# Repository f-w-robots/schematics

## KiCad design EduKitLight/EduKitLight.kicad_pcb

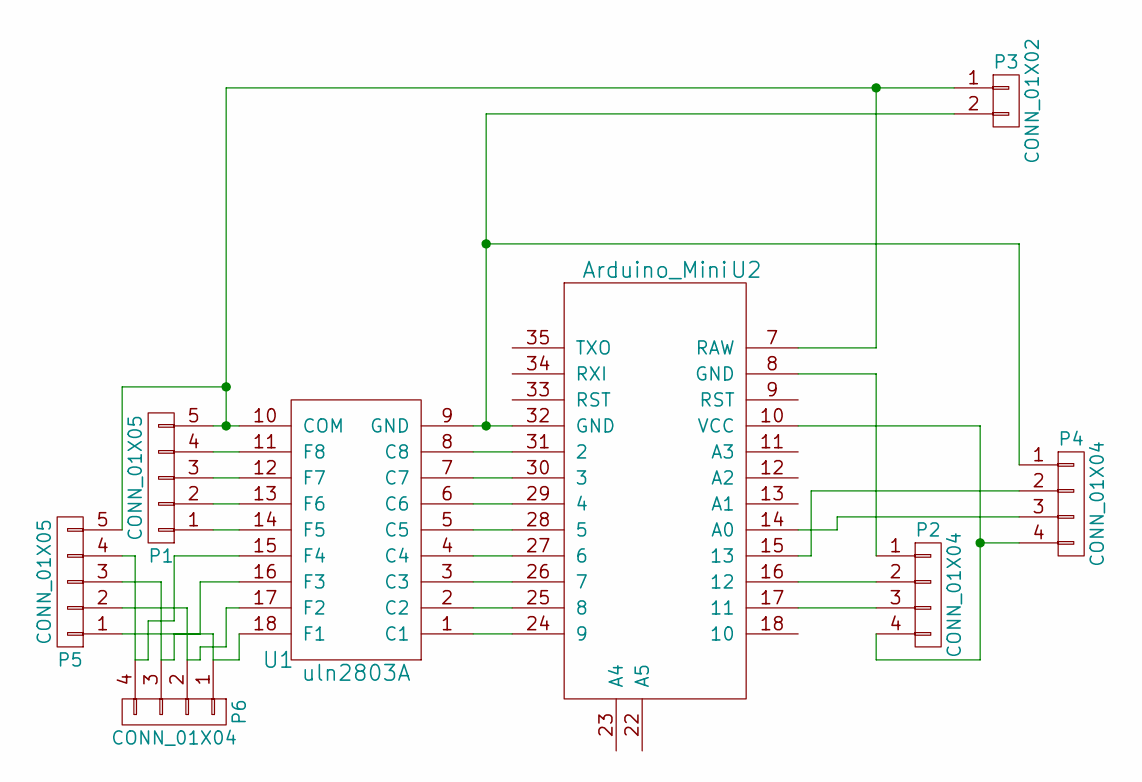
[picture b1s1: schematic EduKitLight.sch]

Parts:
P1, P5: CONN_01X05; Pin_Header_Straight_1x05
P2, P4, P6: CONN_01X04; Pin_Header_Straight_1x04
P3: CONN_01X02; Pin_Header_Straight_1x02
U1: uln2803A; DIP-18_W7.62mm
U2: Arduino_Mini; arduino_mini_pro

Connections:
unnamed: P1.1, U1.14 (F5)
unnamed: P1.2, U1.13 (F6)
unnamed: P1.3, U1.12 (F7)
unnamed: P1.4, U1.11 (F8)
unnamed: P1.5, P3.1, P5.5, U1.10 (COM), U2.7 (RAW)
unnamed: P2.1, U2.8 (GND)
unnamed: P2.2, U2.16 (12)
unnamed: P2.3, U2.17 (11)
unnamed: P2.4, P4.4, U2.10 (VCC)
unnamed: P3.2, P4.1, U1.9 (GND), U2.32 (GND)
unnamed: P4.2, U2.15 (13)
unnamed: P4.3, U2.14 (A0)
unnamed: P5.1, P6.1, U1.18 (F1)
unnamed: P5.2, P6.2, U1.17 (F2)
unnamed: P5.3, P6.3, U1.16 (F3)
unnamed: P5.4, P6.4, U1.15 (F4)
unnamed: U1.1 (C1), U2.24 (9)
unnamed: U1.2 (С2), U2.25 (8)
unnamed: U1.3 (С3), U2.26 (7)
unnamed: U1.4 (С4), U2.27 (6)
unnamed: U1.5 (С5), U2.28 (5)
unnamed: U1.6 (С6), U2.29 (4)
unnamed: U1.7 (С7), U2.30 (3)
unnamed: U1.8 (С8), U2.31 (2)

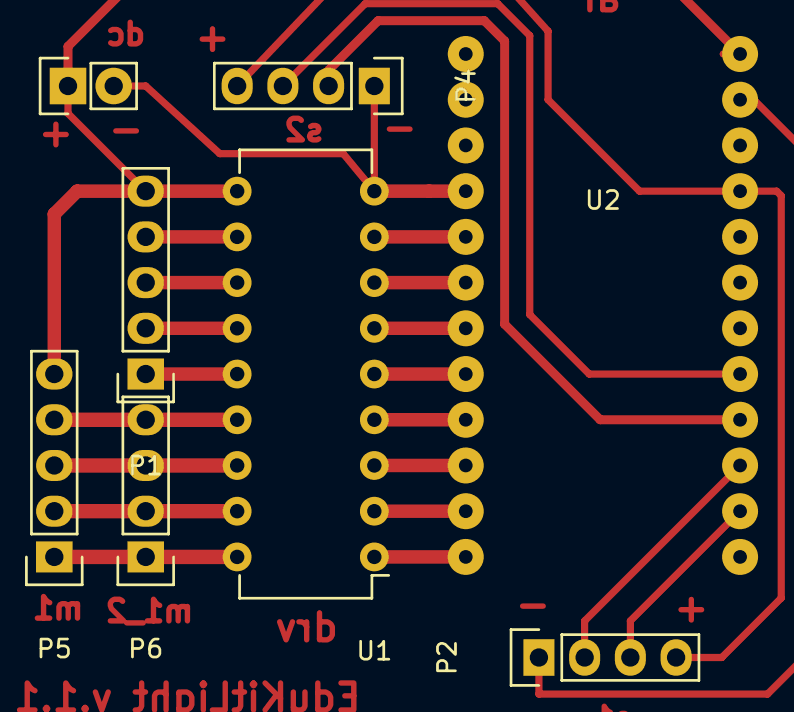
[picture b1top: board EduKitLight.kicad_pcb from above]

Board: 2 copper layers, 8 parts (0 on the bottom side), 24 nets.

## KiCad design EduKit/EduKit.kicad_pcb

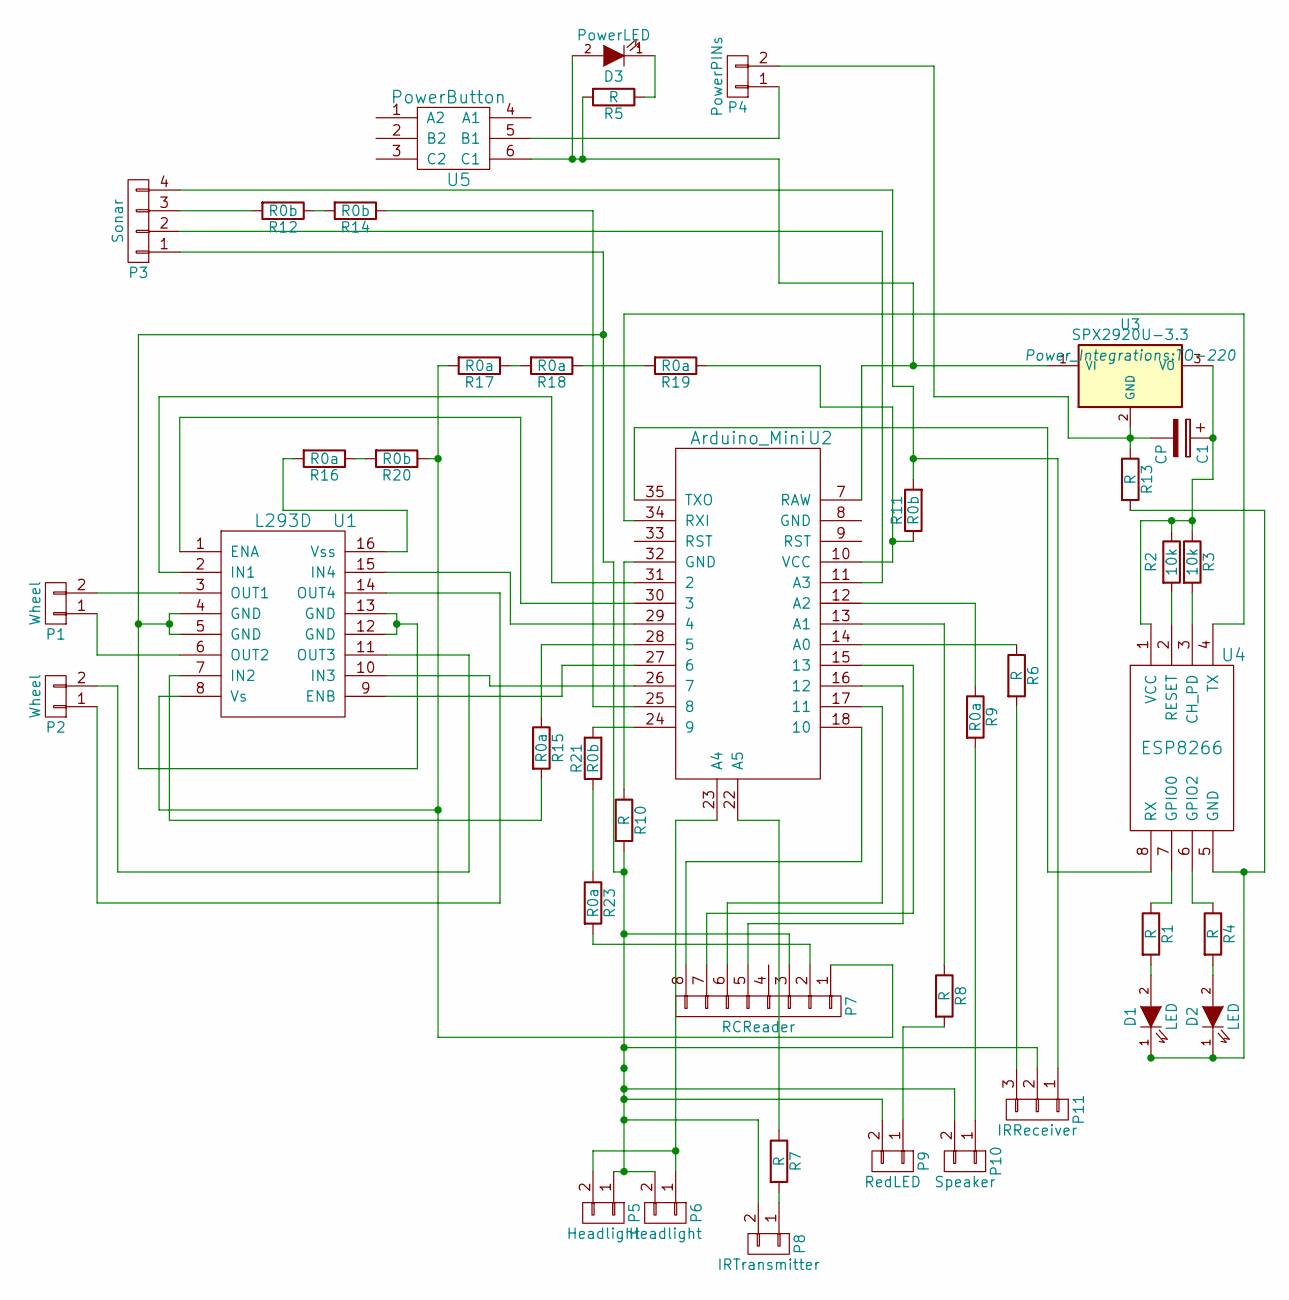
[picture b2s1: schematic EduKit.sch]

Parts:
C1: CP; CPR10X16
D1, D2: LED; LED-5MM
D3: PowerLED; LED-5MM
P1, P2: Wheel; Pin_Header_Straight_1x02
P3: Sonar; Pin_Header_Straight_1x04
P4: PowerPINs; Pin_Header_Straight_1x02
P5, P6: Headlight; Pin_Header_Straight_1x02
P7: RCReader; Pin_Header_Straight_1x08
P8: IRTransmitter; Pin_Header_Straight_1x02
P9: RedLED; Pin_Header_Straight_1x02
P10: Speaker; Pin_Header_Straight_1x02
P11: IRReceiver; Pin_Header_Straight_1x03
R1, R4, R5: R; Resistor_Horizontal_RM7mm
R2, R3: 10k; Resistor_Horizontal_RM7mm
R6, R7, R8, R10, R13: R; R_1206
R9, R15, R16, R18, R19, R23: R0a; R_1206
R11, R12, R14, R20, R21: R0b; R_2512
R17: R0a; R_2512
U1: L293D; DIP-16_W7.62mm
U2: Arduino_Mini; arduino_mini_pro
U3: SPX2920U-3.3; TO-220
U4: ESP8266
U5: PowerButton; button

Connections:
unnamed: C1.1, R2.1, R3.1, U3.3 (VO), U4.1 (VCC)
unnamed: C1.2, P4.2, R13.1, U3.2 (GND)
unnamed: D1.1 (K), D2.1 (K), R13.2, U4.5 (GND)
unnamed: D1.2 (A), R1.2
unnamed: D2.2 (A), R4.2
unnamed: D3.1 (K), R5.1
unnamed: D3.2 (A), R5.2, U2.7 (RAW), U3.1 (VI), U5.6 (C1)
unnamed: P1.1, U1.6 (OUT2)
unnamed: P1.2, U1.3 (OUT1)
unnamed: P2.1, U1.14 (OUT4)
unnamed: P2.2, U1.11 (OUT3)
unnamed: P3.2, U2.11 (A3)
unnamed: P3.3, R12.2
unnamed: P4.1, U5.5 (B1)
unnamed: P5.2, P6.1, U2.23 (A4)
unnamed: P7.1, R17.2, R20.1, U1.8 (Vs)
unnamed: P7.2, R23.2
unnamed: P7.5, U2.16 (12)
unnamed: P7.6, U2.17 (11)
unnamed: P7.7, U2.15 (13)
unnamed: P7.8, U2.18 (10)
unnamed: P8.1, R7.2
unnamed: P9.1, R8.2
unnamed: P10.1, R9.2
unnamed: P3.1, P5.1, P6.2, P7.3, P8.2, P9.2, P10.2, P11.2, R10.2, U1.4 (GND), U1.5 (GND), U1.12 (GND), U1.13 (GND)
unnamed: P3.4, P11.1, R11.2
unnamed: P11.3, R6.2
unnamed: R1.1, U4.7 (GPIO0)
unnamed: R2.2, U4.2 (RESET)
unnamed: R3.2, U4.3 (CH_PD)
unnamed: R4.1, U4.6 (GPIO2)
unnamed: R6.1, U2.14 (A0)
unnamed: R7.1, U2.22 (A5)
unnamed: R8.1, U2.13 (A1)
unnamed: R9.1, U2.12 (A2)
unnamed: R10.1, U2.32 (GND)
unnamed: R11.1, R19.1, U2.10 (VCC)
unnamed: R12.1, R14.2
unnamed: R14.1, U2.25 (8)
unnamed: R15.1, U2.28 (5)
unnamed: R15.2, U1.7 (IN2)
unnamed: R16.1, R20.2
unnamed: R16.2, U1.16 (Vss)
unnamed: R17.1, R18.2
unnamed: R18.1, R19.2
unnamed: R21.1, R23.1
unnamed: R21.2, U2.24 (9)
unnamed: U1.1 (ENA), U2.30 (3)
unnamed: U1.2 (IN1), U2.31 (2)
unnamed: U1.9 (ENB), U2.27 (6)
unnamed: U1.10 (IN3), U2.26 (7)
unnamed: U1.15 (IN4), U2.29 (4)
unnamed: U2.34 (RXI), U4.4 (TX)
unnamed: U2.35 (TXO), U4.8 (RX)

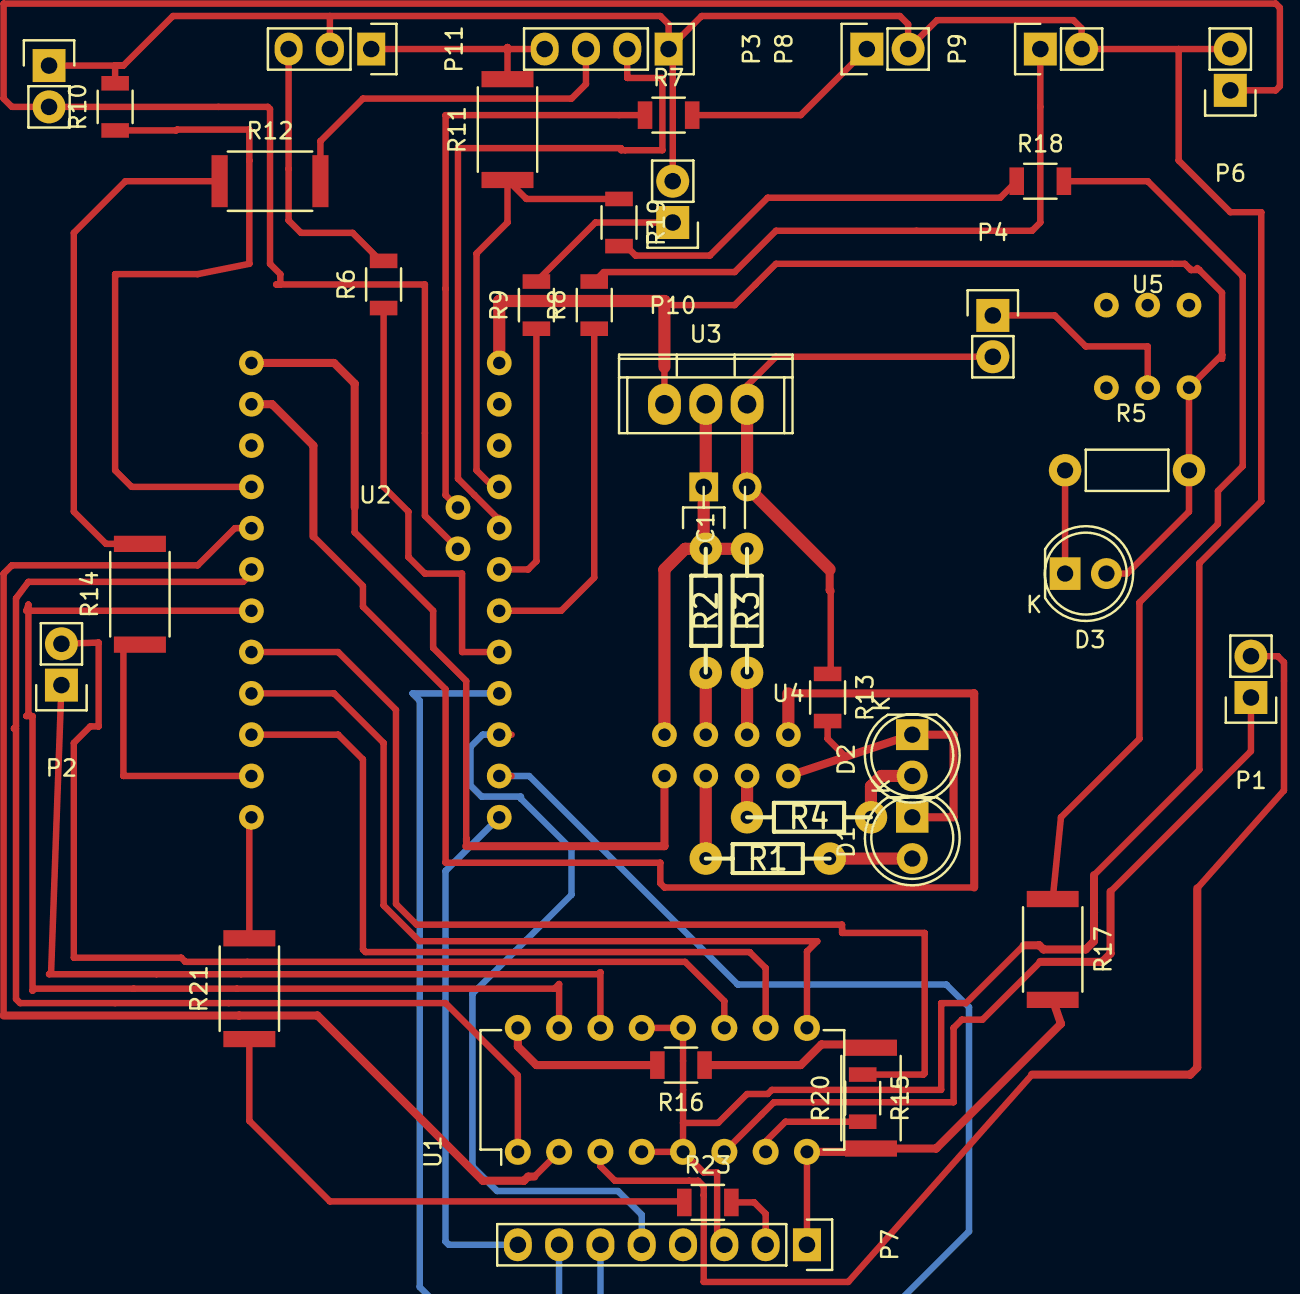
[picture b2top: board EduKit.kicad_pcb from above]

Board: 2 copper layers, 42 parts (0 on the bottom side), 54 nets.

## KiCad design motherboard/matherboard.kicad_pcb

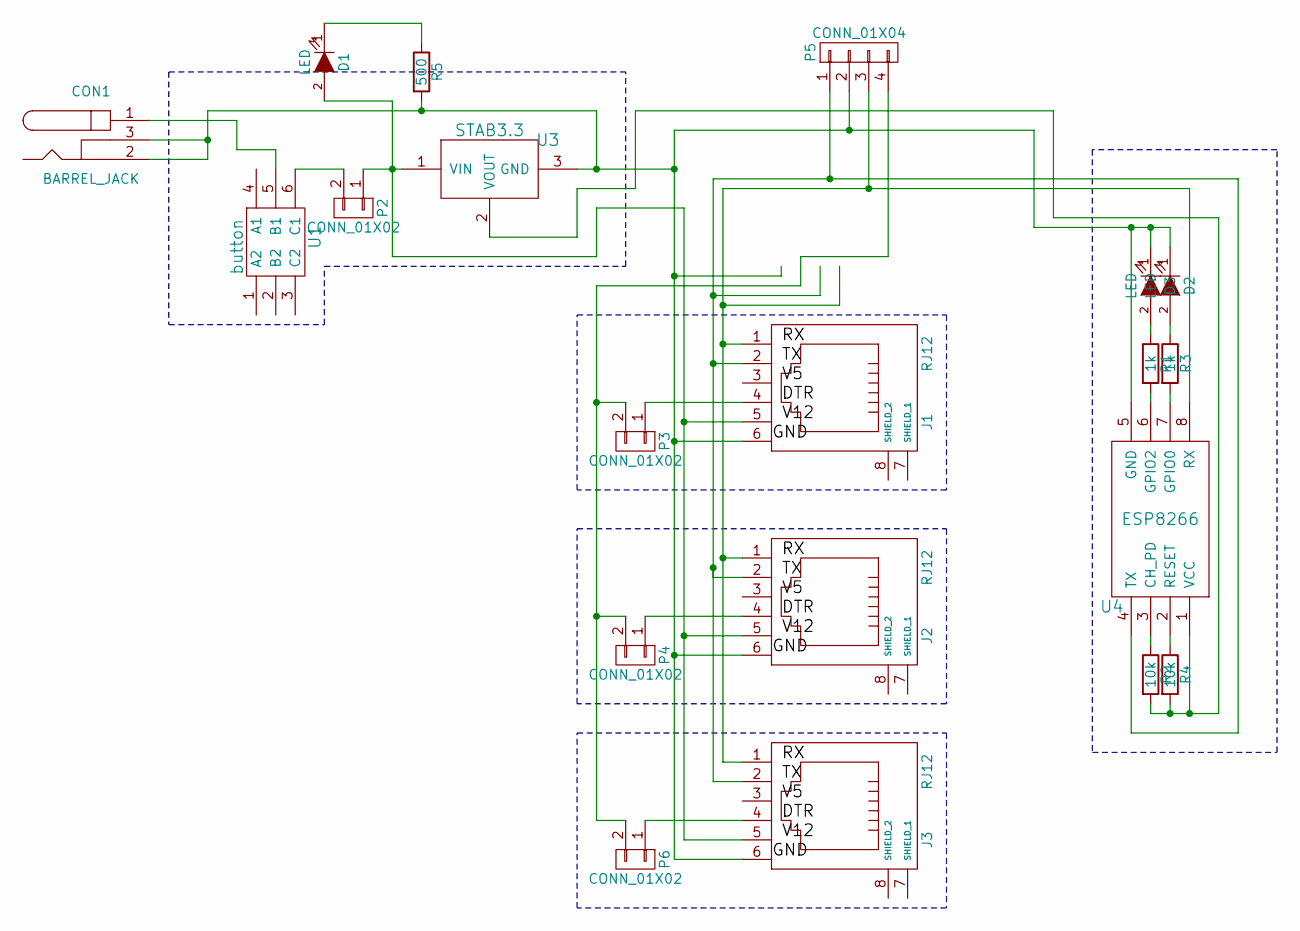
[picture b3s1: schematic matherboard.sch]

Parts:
CON1: BARREL_JACK
D1, D2, D3: LED; LED-3MM
J1, J2, J3: RJ12; RJ12_E
P2, P3, P4, P6: CONN_01X02; Pin_Header_Straight_1x02
P5: CONN_01X04; Pin_Header_Straight_1x04
R1, R3: 1k; Resistor_Horizontal_RM7mm
R2, R4: 10k; rc03_vert
R5: 500; rc03_vert
U1: button
U3: STAB3.3; PINHEAD1-3
U4: ESP8266; esp8266

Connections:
unnamed: CON1.1, U1.5 (B1)
unnamed: CON1.2, CON1.3, D2.1 (K), D3.1 (K), J1.6, J2.6, J3.6, P5.2, R5.2, U3.3 (GND), U4.5 (GND)
unnamed: D1.1 (K), R5.1
unnamed: D1.2 (A), J1.5, J2.5, J3.5, P2.1, U3.1 (VIN)
unnamed: D2.2 (A), R3.1
unnamed: D3.2 (A), R1.1
unnamed: J1.1, J2.1, J3.1, P5.3, U4.8 (RX)
unnamed: J1.2, J2.2, J3.2, P5.1, U4.4 (TX)
unnamed: J1.4, P3.1
unnamed: J2.4, P4.1
unnamed: J3.4, P6.1
unnamed: P2.2, U1.6 (C1)
unnamed: P3.2, P4.2, P5.4, P6.2
unnamed: R1.2, U4.6 (GPIO2)
unnamed: R2.1, U4.3 (CH_PD)
unnamed: R2.2, R4.2, U3.2 (VOUT), U4.1 (VCC)
unnamed: R3.2, U4.7 (GPIO0)
unnamed: R4.1, U4.2 (RESET)

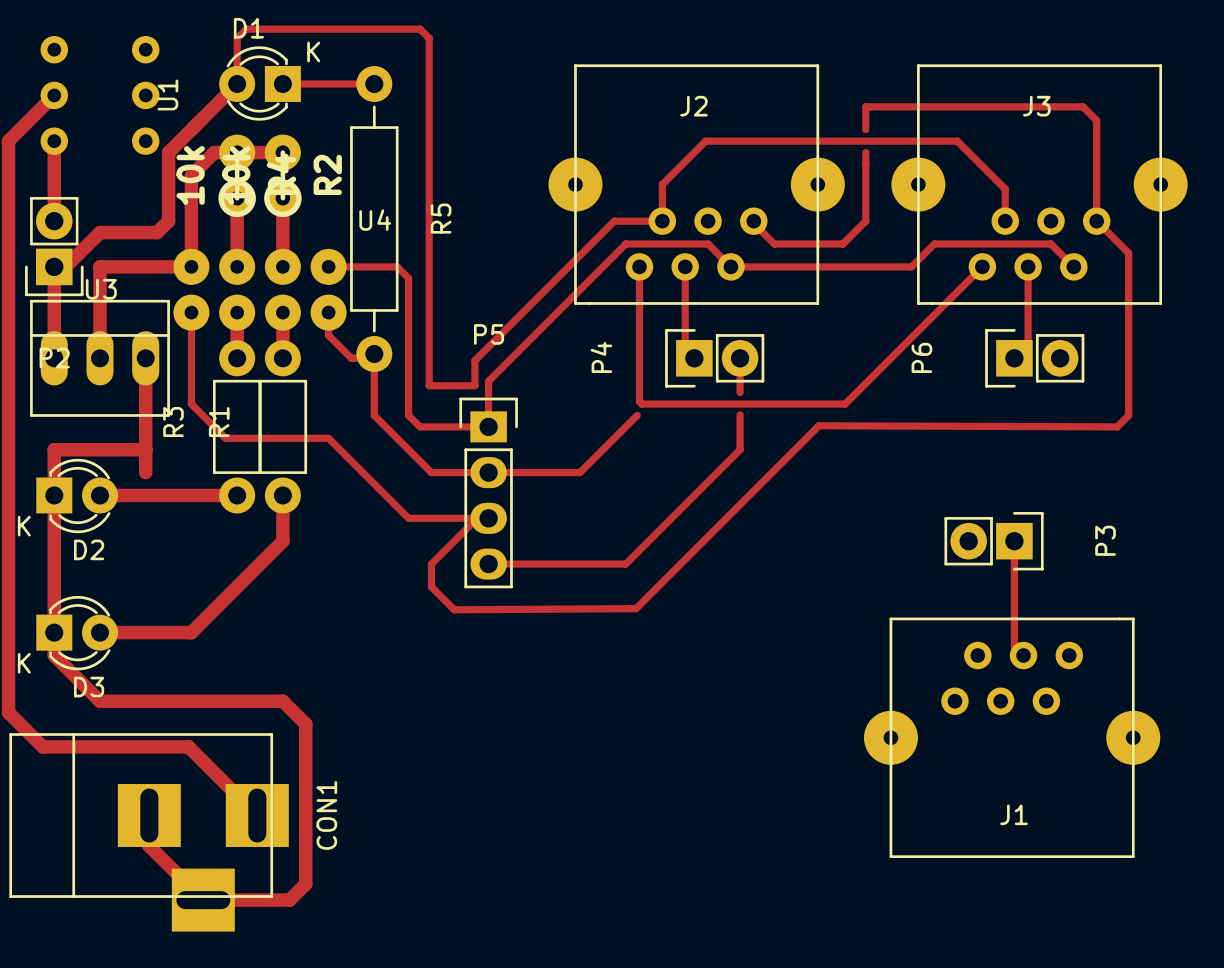
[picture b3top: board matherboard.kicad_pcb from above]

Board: 2 copper layers, 20 parts (0 on the bottom side), 18 nets.

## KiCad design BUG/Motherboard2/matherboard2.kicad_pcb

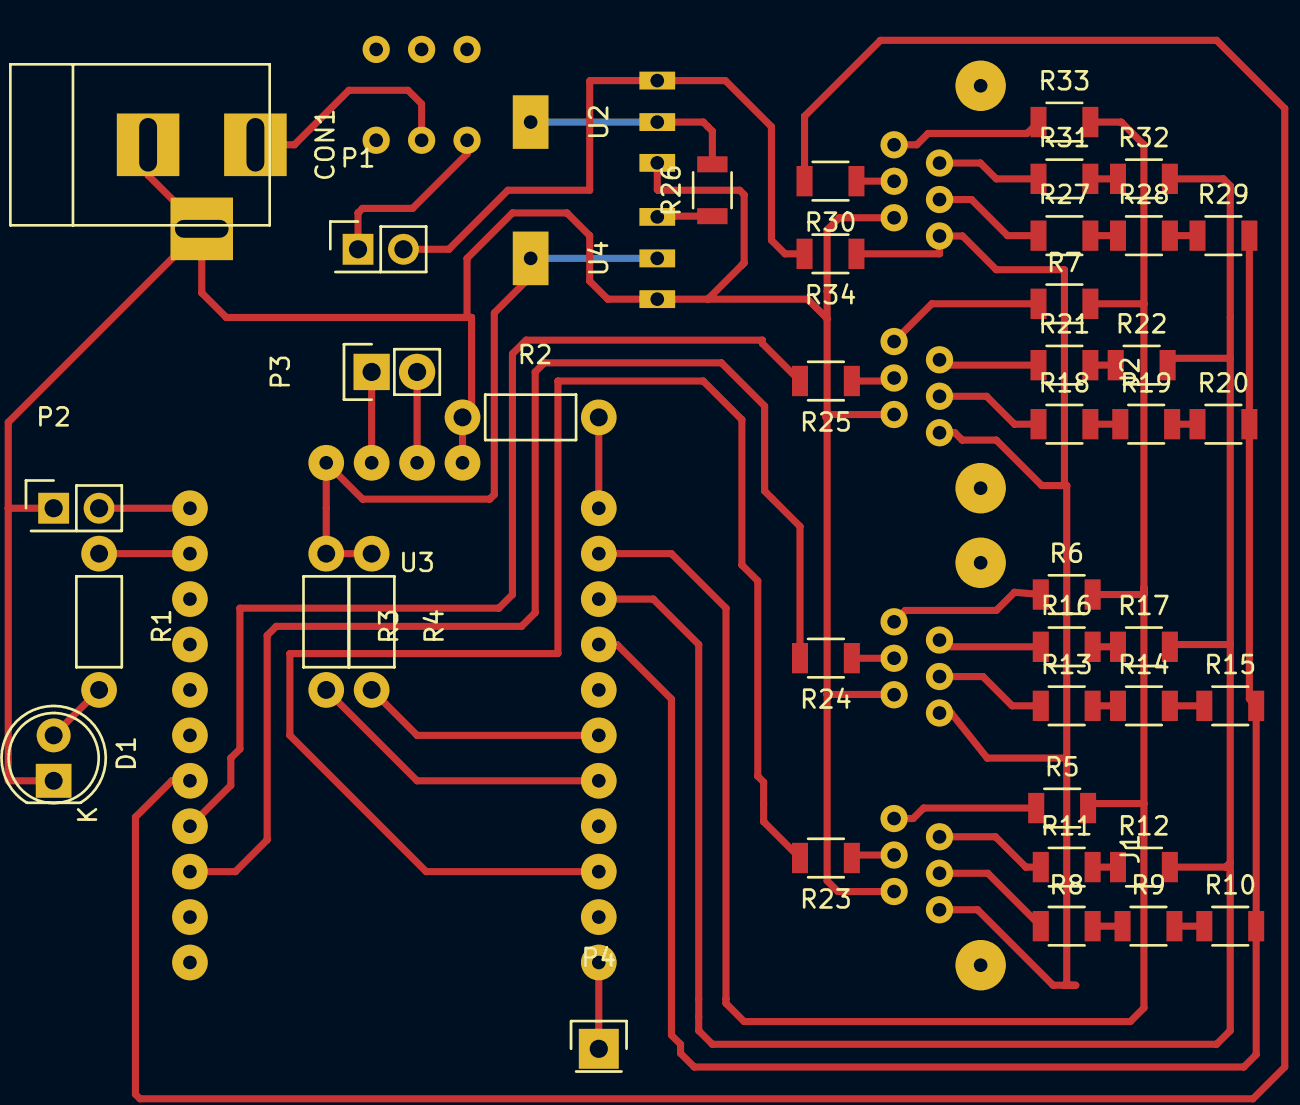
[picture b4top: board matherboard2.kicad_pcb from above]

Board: 2 copper layers, 46 parts (1 on the bottom side), 52 nets.

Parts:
CON1: BARREL_JACK
D1: LED; LED-5MM
J1, J2: RJ12double
P1: ON/OFF; Pin_Header_Straight_2x01
P2: FW; Pin_Header_Straight_2x01
P3: RXTX; Pin_Header_Straight_1x02
P4: GND; Pin_Header_Straight_1x01
R1: 1k; Resistor_Horizontal_RM7mm
R2: 10K; Resistor_Horizontal_RM7mm
R3, R4: 10k; Resistor_Horizontal_RM7mm
R5, R6, R7, R8, R9, R10, R11, R12, R13, R14, R15, R16, R17, R18, R19, R20, R21, R22, R23, R24, R25, R26, R27, R28, R29, R30, R31, R32, R33, R34: 0; R_1206
U1: BUTTON; button
U2: AP1117-5; SMD-stab
U3: ESP-201; ESP201
U4: AP1117-3; SMD-stab

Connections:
unnamed: CON1.1, U1.2
unnamed: CON1.2, CON1.3, D1.1, J1.2, J1.10, J2.2, J2.10, P2.1, R2.1, U2.1, U3.4, U4.1
unnamed: D1.2, R1.2
unnamed: J1.1, J1.9, J2.1, J2.9, R34.1
unnamed: J1.3, R13.1
unnamed: J1.4, R24.1
unnamed: J1.5, R16.1
unnamed: J1.6, R6.1
unnamed: J1.11, R8.1
unnamed: J1.12, R23.1
unnamed: J1.13, R11.1
unnamed: J1.14, R5.1
unnamed: J2.3, R27.1
unnamed: J2.4, R30.1
unnamed: J2.5, R31.1
unnamed: J2.6, R33.1
unnamed: J2.11, R18.1
unnamed: J2.12, R25.1
unnamed: J2.13, R21.1
unnamed: J2.14, R7.1
unnamed: P1.1, U1.3
unnamed: P1.2, R34.2, U2.3
unnamed: P2.2, U3.5
unnamed: P3.1, U3.2
unnamed: P3.2, U3.3
unnamed: P4.1, U3.16
unnamed: R1.1, U3.6
unnamed: R2.2, U3.26
unnamed: R3.1, R4.1, U3.1, U4.2
unnamed: R3.2, U3.20
unnamed: R4.2, U3.21
unnamed: R8.2, R9.1
unnamed: R9.2, R10.1
unnamed: R10.2, R15.2, R20.2, R29.2, U3.23
unnamed: R11.2, R12.1
unnamed: R12.2, R17.2, R22.2, R32.2, U3.24
unnamed: R13.2, R14.1
unnamed: R14.2, R15.1
unnamed: R16.2, R17.1
unnamed: R18.2, R19.1
unnamed: R19.2, R20.1
unnamed: R21.2, R22.1
unnamed: R23.2, U3.18
unnamed: R24.2, U3.13
unnamed: R25.2, U3.12
unnamed: R26.1, U4.3
unnamed: R26.2, U2.2
unnamed: R27.2, R28.1
unnamed: R28.2, R29.1
unnamed: R30.2, U3.11
unnamed: R31.2, R32.1
unnamed: R5.2, R6.2, R7.2, R33.2, U3.25

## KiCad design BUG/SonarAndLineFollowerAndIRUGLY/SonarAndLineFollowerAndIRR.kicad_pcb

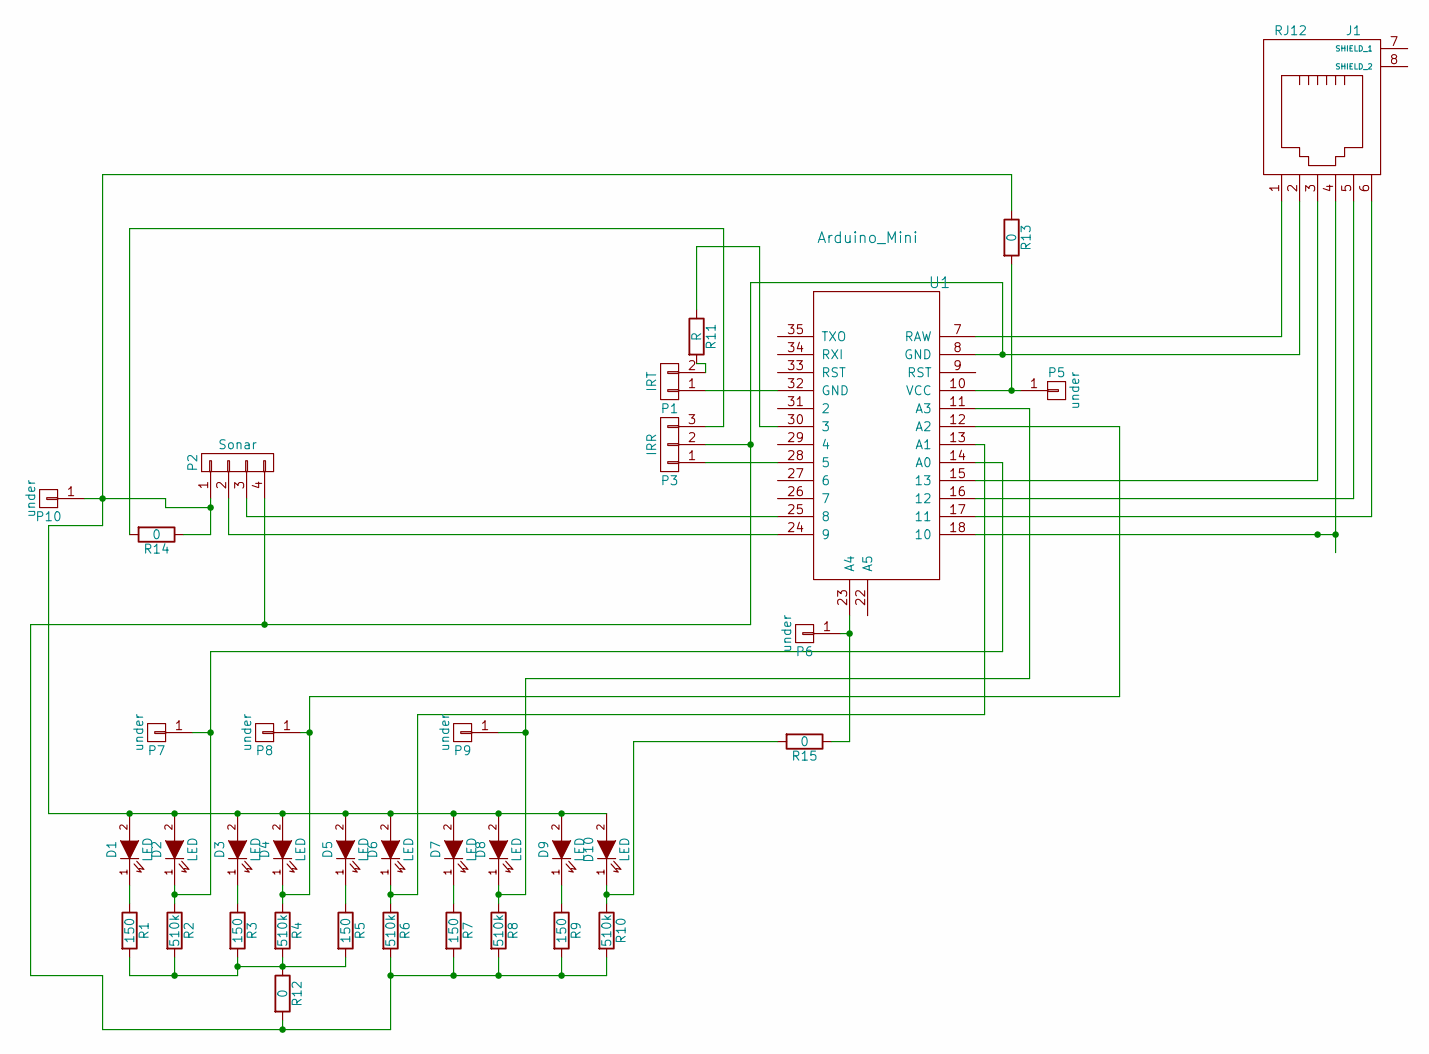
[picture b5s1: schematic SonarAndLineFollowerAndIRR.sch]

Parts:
D1, D2, D3, D4, D5, D6, D7, D8, D9, D10: LED; LED-3MM
J1: RJ12; RJ12_Client
P1: IRT; Pin_Header_Straight_1x02
P2: Sonar; Pin_Header_Straight_1x04
P3: IRR; Pin_Header_Straight_1x03
P5, P6, P7, P8, P9, P10: under; Pin_Header_Straight_1x01
R1, R3, R5, R7, R9: 150; Resistor_Horizontal_RM7mm
R2, R4, R6, R8, R10: 510k; Resistor_Horizontal_RM7mm
R11: R; Resistor_Horizontal_RM7mm
R12, R13, R14, R15: 0; R_1206
U1: Arduino_Mini; arduino_mini_pro

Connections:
unnamed: D1.1 (K), R1.1
unnamed: D1.2 (A), D2.2 (A), D3.2 (A), D4.2 (A), D5.2 (A), D6.2 (A), D7.2 (A), D8.2 (A), D9.2 (A), D10.2 (A), P2.1, P10.1, R13.1, R14.1
unnamed: D2.1 (K), P7.1, R2.1, U1.14 (A0)
unnamed: D3.1 (K), R3.1
unnamed: D4.1 (K), P8.1, R4.1, U1.12 (A2)
unnamed: D5.1 (K), R5.1
unnamed: D6.1 (K), R6.1, U1.13 (A1)
unnamed: D7.1 (K), R7.1
unnamed: D8.1 (K), P9.1, R8.1, U1.11 (A3)
unnamed: D9.1 (K), R9.1
unnamed: D10.1 (K), R10.1, R15.2
unnamed: J1.1, U1.7 (RAW)
unnamed: J1.2, P2.4, P3.2, R6.2, R7.2, R8.2, R9.2, R10.2, R12.2, U1.8 (GND)
unnamed: J1.3, U1.15 (13)
unnamed: J1.4, U1.18 (10)
unnamed: J1.5, U1.16 (12)
unnamed: J1.6, U1.17 (11)
unnamed: P1.1, U1.32 (GND)
unnamed: P1.2, R11.2
unnamed: P2.2, U1.24 (9)
unnamed: P2.3, U1.25 (8)
unnamed: P3.1, U1.28 (5)
unnamed: P3.3, R14.2
unnamed: P5.1, R13.2, U1.10 (VCC)
unnamed: P6.1, R15.1, U1.23 (A4)
unnamed: R1.2, R2.2, R3.2, R4.2, R5.2, R12.1
unnamed: R11.1, U1.30 (3)

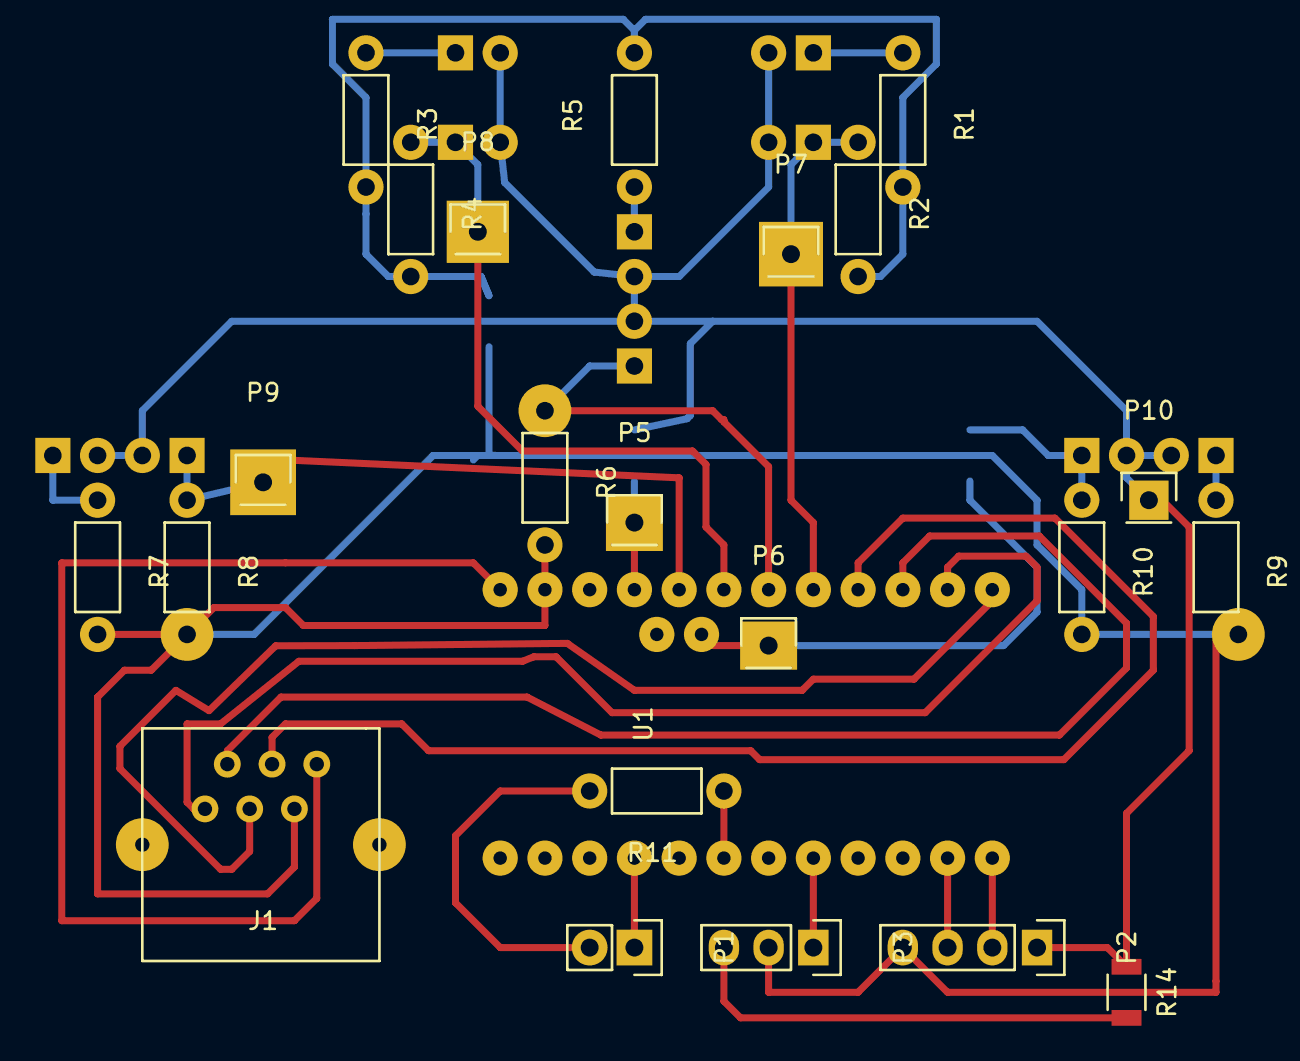
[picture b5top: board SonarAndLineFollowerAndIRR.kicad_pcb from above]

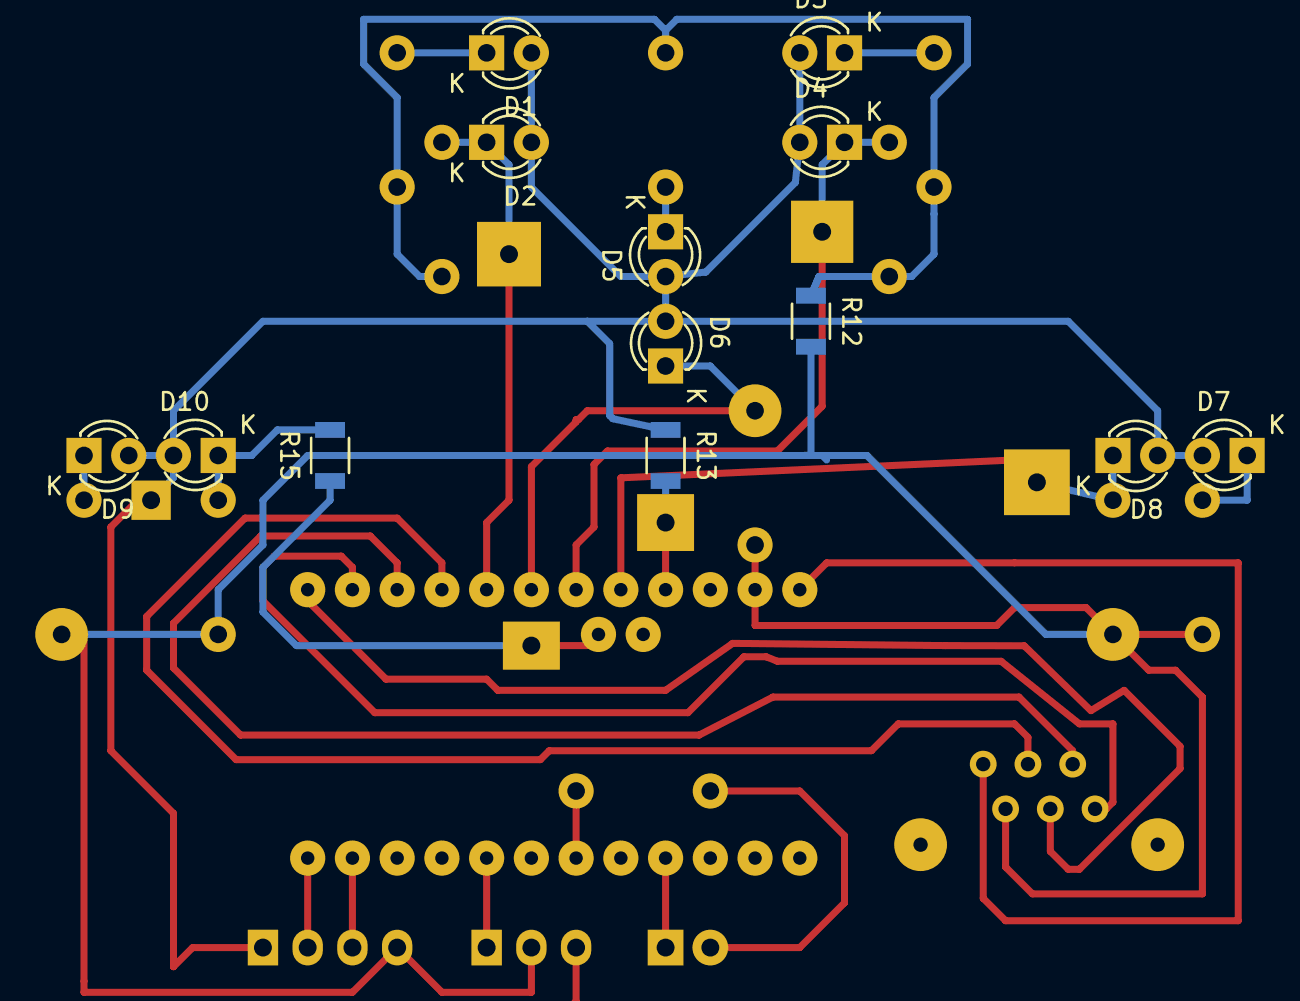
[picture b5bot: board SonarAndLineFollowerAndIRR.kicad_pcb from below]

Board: 2 copper layers, 36 parts (13 on the bottom side), 27 nets.

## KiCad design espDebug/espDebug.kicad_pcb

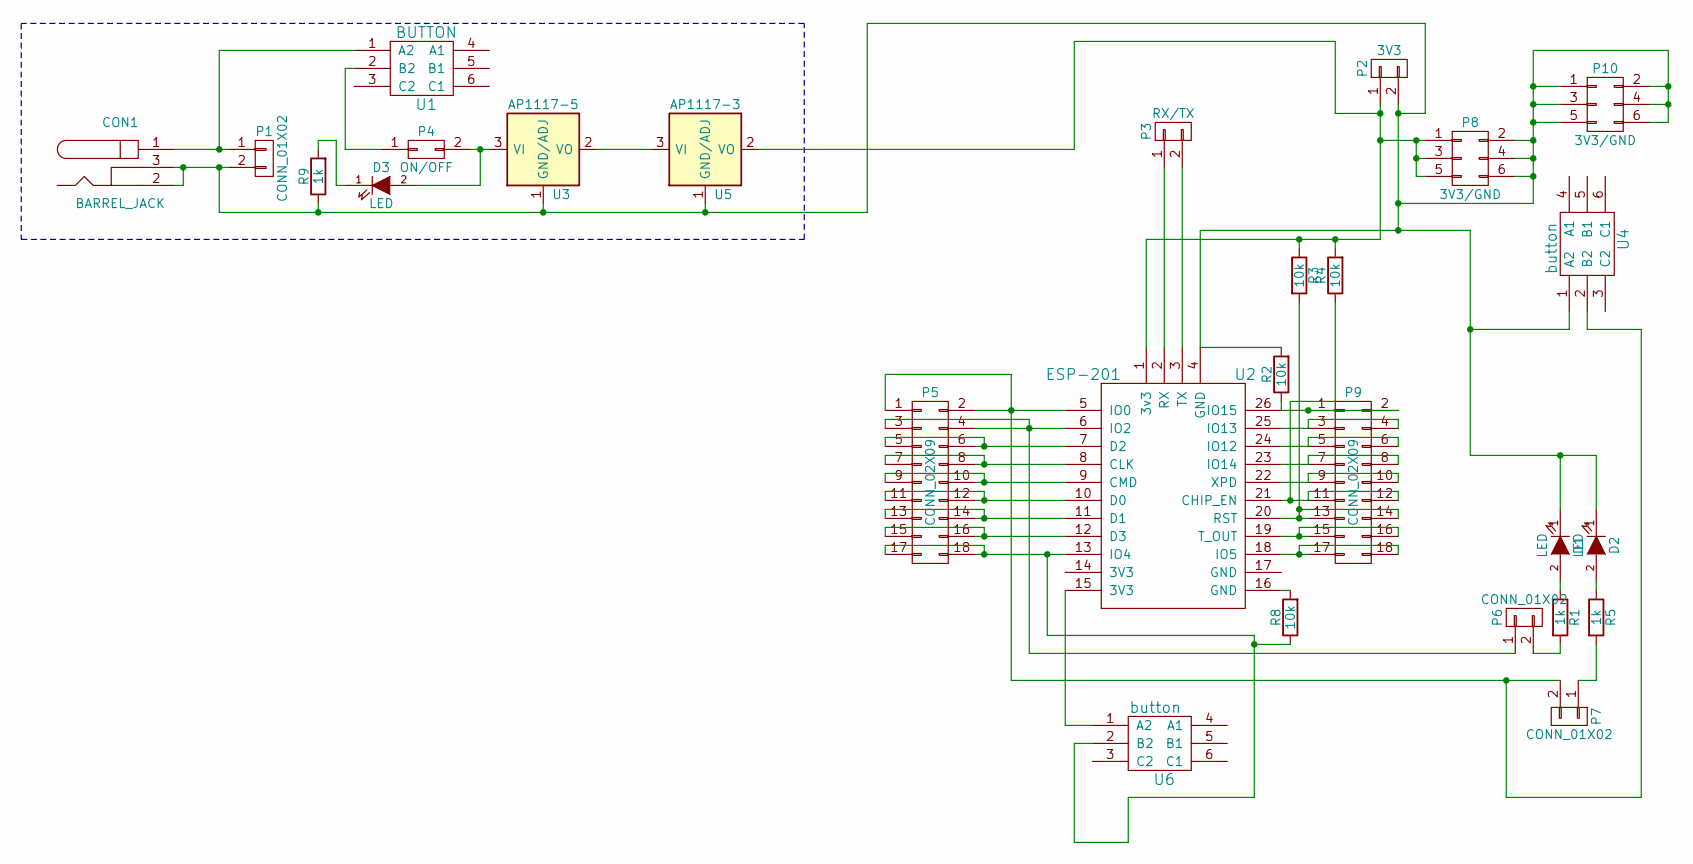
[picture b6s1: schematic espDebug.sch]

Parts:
CON1: BARREL_JACK
D1, D2, D3: LED; LED-3MM
P1, P6, P7: CONN_01X02; Pin_Header_Straight_1x02
P2: 3V3; Pin_Header_Straight_1x02
P3: RX/TX; Pin_Header_Straight_1x02
P4: ON/OFF; Pin_Header_Straight_2x01
P5, P9: CONN_02X09; Pin_Header_Straight_2x09
P8, P10: 3V3/GND; Pin_Header_Straight_2x03
R1, R5, R9: 1k; Resistor_Horizontal_RM7mm
R2, R3, R4, R8: 10k; Resistor_Horizontal_RM7mm
U1: BUTTON; button
U2: ESP-201; ESP201
U3: AP1117-5; SMD-stab
U4, U6: button
U5: AP1117-3; SMD-stab

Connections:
unnamed: CON1.1, P1.1, U1.1 (A2)
unnamed: CON1.2, CON1.3, D1.1 (K), D2.1 (K), P1.2, P2.2, P8.2, P8.4, P8.6, P10.1, P10.2, P10.3, P10.4, P10.5, P10.6, R2.2, R9.1, U2.4 (GND), U3.1 (GND/ADJ), U4.1 (A2), U5.1 (GND/ADJ)
unnamed: D1.2 (A), R1.1
unnamed: D2.2 (A), R5.1
unnamed: D3.1 (K), R9.2
unnamed: D3.2 (A), P4.2, U3.3 (VI)
unnamed: P2.1, P8.1, P8.3, P8.5, R3.1, R4.2, U2.1 (3v3), U5.2 (VO)
unnamed: P3.1, U2.2 (RX)
unnamed: P3.2, U2.3 (TX)
unnamed: P4.1, U1.2 (B2)
unnamed: P5.1, P5.2, P7.2, U2.5 (IO0), U4.2 (B2)
unnamed: P5.3, P5.4, P6.1, U2.6 (IO2)
unnamed: P5.5, P5.6, U2.7 (D2)
unnamed: P5.7, P5.8, U2.8 (CLK)
unnamed: P5.9, P5.10, U2.9 (CMD)
unnamed: P5.11, P5.12, U2.10 (D0)
unnamed: P5.13, P5.14, U2.11 (D1)
unnamed: P5.15, P5.16, U2.12 (D3)
unnamed: P5.17, P5.18, R8.1, U2.13 (IO4), U6.2 (B2)
unnamed: P6.2, R1.2
unnamed: P7.1, R5.2
unnamed: P9.1, P9.2, R2.1, U2.26 (IO15)
unnamed: P9.3, P9.4, U2.25 (IO13)
unnamed: P9.5, P9.6, U2.24 (IO12)
unnamed: P9.7, P9.8, U2.23 (IO14)
unnamed: P9.9, P9.10, U2.22 (XPD)
unnamed: P9.11, P9.12, R4.1, U2.21 (CHIP_EN)
unnamed: P9.13, P9.14, R3.2, U2.20 (RST)
unnamed: P9.15, P9.16, U2.19 (T_OUT)
unnamed: P9.17, P9.18, U2.18 (IO5)
unnamed: R8.2, U2.16 (GND)
unnamed: U2.15 (3V3), U6.1 (A2)
unnamed: U3.2 (VO), U5.3 (VI)

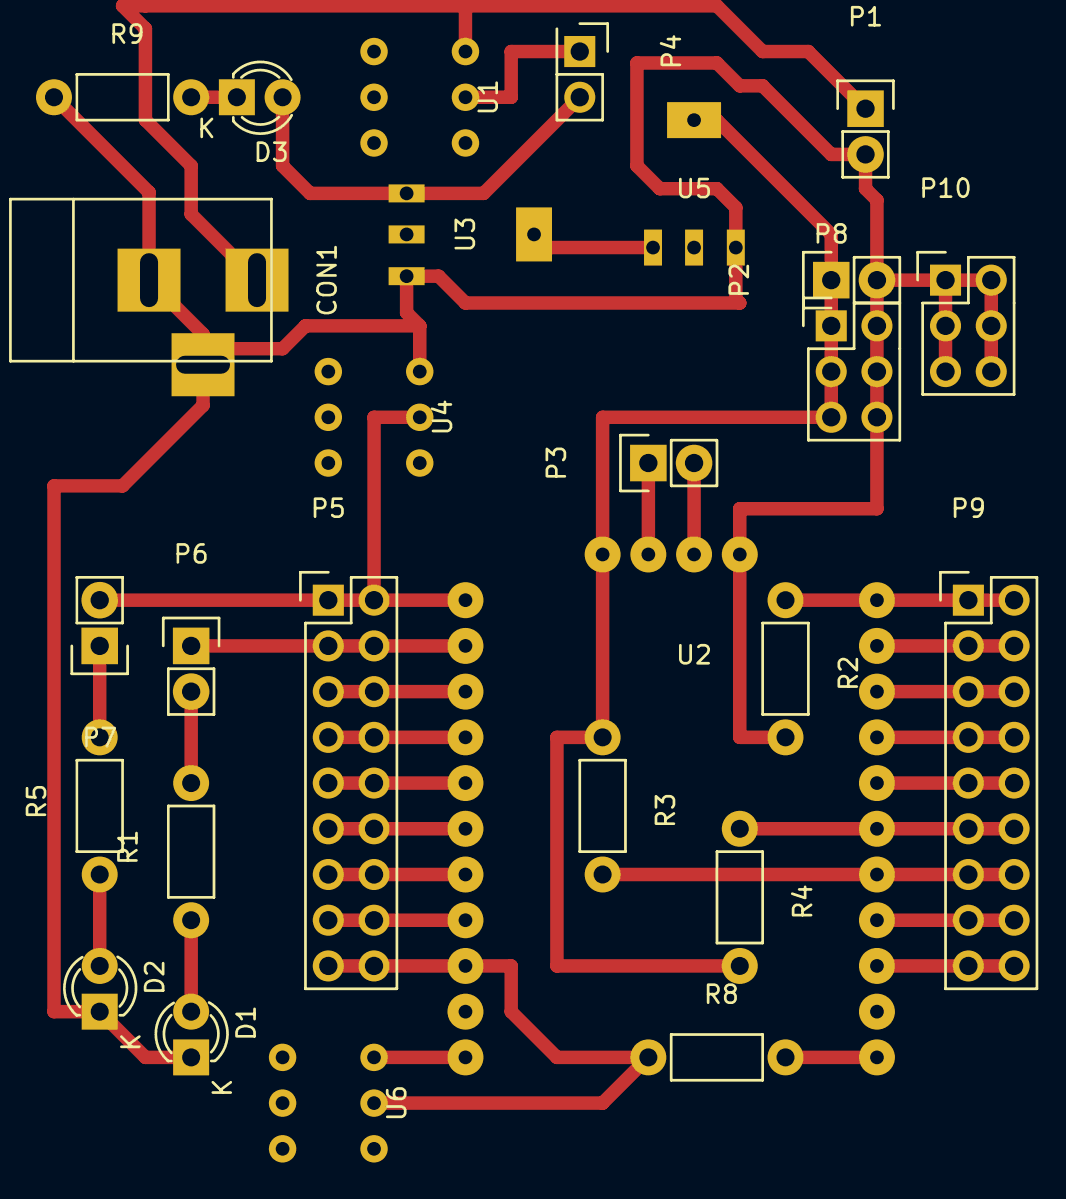
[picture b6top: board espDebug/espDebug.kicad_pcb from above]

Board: 2 copper layers, 27 parts (0 on the bottom side), 33 nets.
